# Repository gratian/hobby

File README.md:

# Hobby Projects

* kicad - electronics

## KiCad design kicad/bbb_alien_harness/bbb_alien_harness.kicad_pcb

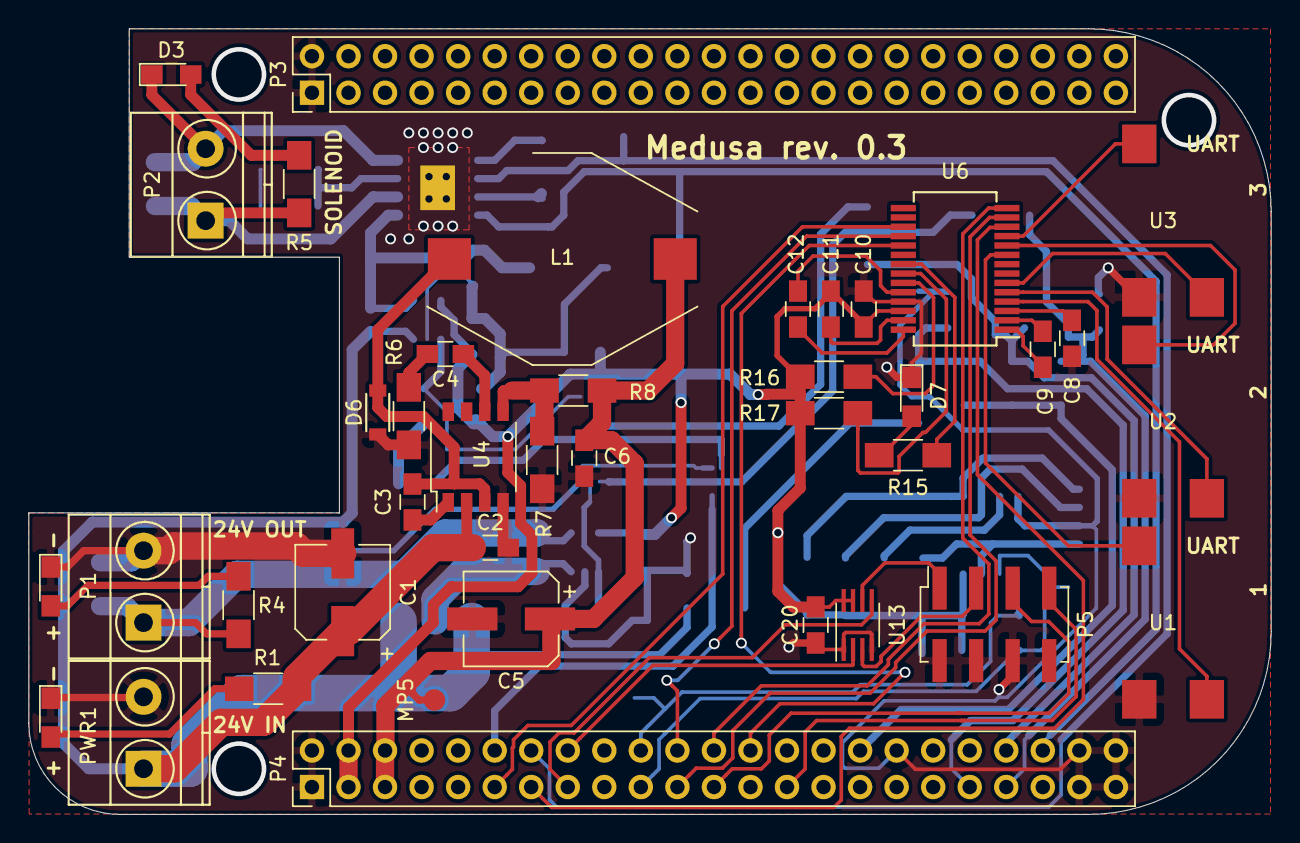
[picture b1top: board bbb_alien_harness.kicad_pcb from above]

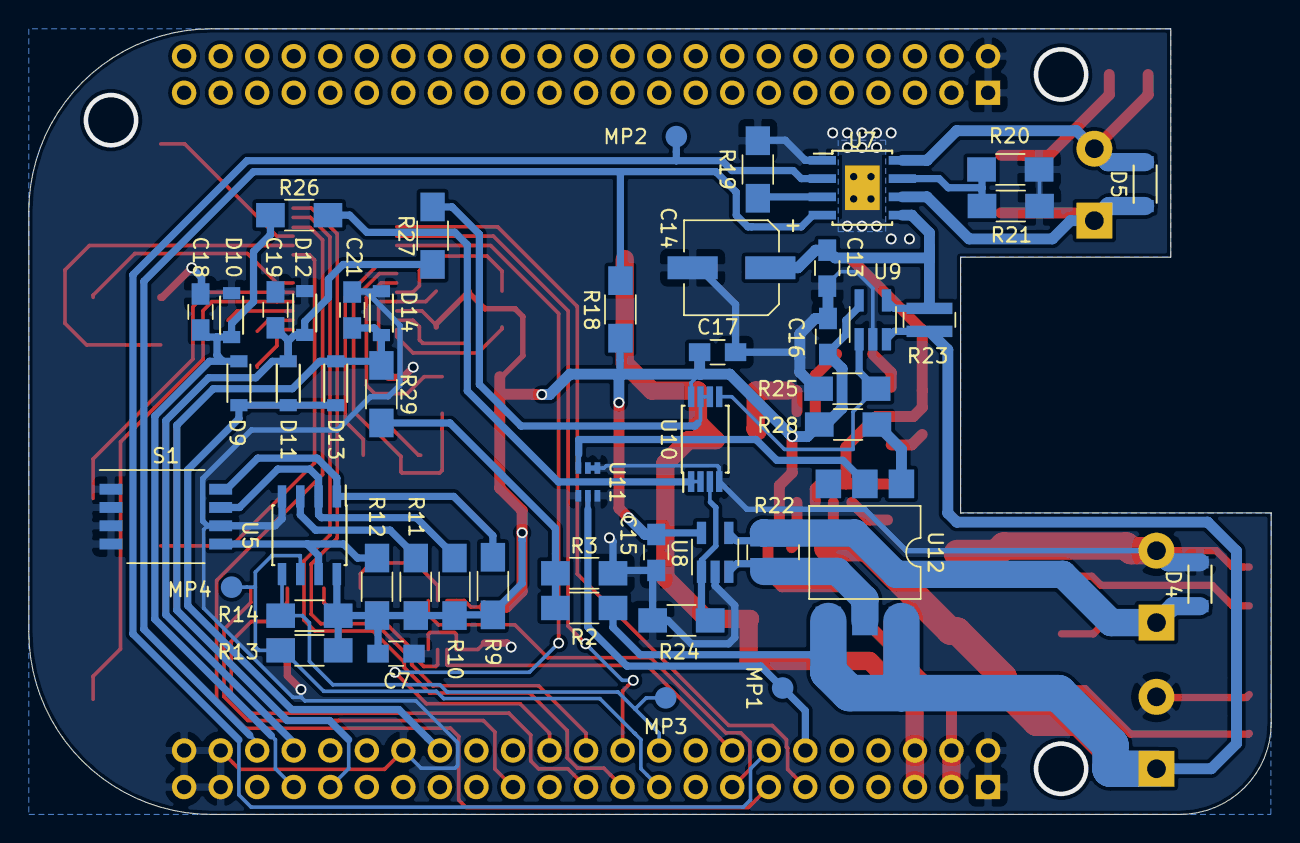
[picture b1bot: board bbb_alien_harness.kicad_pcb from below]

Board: 2 copper layers, 86.4 x 54.6 mm, 89 parts (49 on the bottom side), 67 nets.

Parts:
C1, C14: 47uF; CP_Elec_6.3x5.8
C2: 10uF; C_0805_HandSoldering
C3: 10nF; C_0805_HandSoldering
C4: 2.2nF; C_0805_HandSoldering
C5: 100uF; CP_Elec_6.3x5.8
C6: 1uF; C_0805_HandSoldering
C7, C8, C9, C10, C11, C12, C13, C15, C16, C17, C20: 0.1uF; C_0805_HandSoldering
C18, C19, C21: 1nF; C_0805_HandSoldering
D1: LXT0805YW; LED_0805_HandSoldering
D2, D7: LXT0805GW; LED_0805_HandSoldering
D3: D_1112H; LED_0805_HandSoldering
D4, D5, D6, D9, D10, D11, D12, D13, D14: DB2W40300L; SMD-Mini2-F3-B
L1: 33uH; L_Bourns-PM5022-330M-RC
MP1: SSR EN; Measurement_Point_Round-SMD-Pad_Small
MP2: PWM; Measurement_Point_Round-SMD-Pad_Small
MP3: I2C SDA; Measurement_Point_Round-SMD-Pad_Small
MP4: I2C SCL; Measurement_Point_Round-SMD-Pad_Small
MP5: +5V; Measurement_Point_Round-SMD-Pad_Small
P1: 24V OUT; TerminalBlock_Phoenix_MKDS1.5-2pol
P2: SOLENOID; TerminalBlock_Phoenix_MKDS1.5-2pol
P3: P8 on BBB; Pin_Header_Straight_2x23_Pitch2.54mm
P4: P9 on BBB; Pin_Header_Straight_2x23_Pitch2.54mm
P5: CONN_02X04; Socket_Strip_Straight_2x04_Pitch2.54mm_SMD
PWR1: 24V IN; TerminalBlock_Phoenix_MKDS1.5-2pol
R1, R4, R5: 2.4k; R_1206_HandSoldering
R2: 150k; R_1206_HandSoldering
R3, R7, R12, R16, R17, R18: 10k; R_1206_HandSoldering
R6: 8.2k; R_1206_HandSoldering
R8: 52k; R_1206_HandSoldering
R9, R10, R11: 4.7k; R_1206_HandSoldering
R13, R14: 5.6k; R_1206_HandSoldering
R15: 1k; R_1206_HandSoldering
R19: 100k; R_1206_HandSoldering
R20: 1; R_1206_HandSoldering
R21: 2; R_1206_HandSoldering
R22, R23: 0.020; R_0612
R24, R25: 75k; R_1206_HandSoldering
R26, R27, R29: 75; R_1206_HandSoldering
R28: 360; R_1206_HandSoldering
S1: SW_DIP_x4; SW_DIP_x4_W7.62mm_Slide_Copal_CHS-B
U1, U2, U3: SERIAL; SJ1-251X-SMT 2.5mm stereo jack
U4: ACT4065A; SOP-8_4.4x5mm_Pitch1.27mm
U5: 24C256; SOIC-8_3.9x4.9mm_Pitch1.27mm
U6: MAX3243; SSOP-28_5.3x10.2mm_Pitch0.65mm
U7: DRV8872; TI_SO-PowerPAD-8
U8, U9: INA138; SOT-23-5_HandSoldering
U10: AD8542; TSSOP-8_4.4x3mm_Pitch0.65mm
U11: DMC56404; SMini6-F3-B
U12: AQV251A; SMDIP-6_W9.53mm
U13: SN74LVC2G241; SSOP-8_2.95x2.8mm_Pitch0.65mm

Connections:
5V_REG: C5.1, C6.1, L1.2, MP5.1, P4.5, P4.6, R8.1
+3V3: C7.1, C10.2, C11.2, C15.1, C16.1, C17.1, C20.1, P4.3, P4.4, R9.1, R10.1, R11.1, R12.1, R13.1, R14.1, R16.1, R17.1, R18.1, R28.2, U5.8, U6.26, U8.5, U9.5, U10.8, U13.7, U13.8
+24V: C1.1, C2.1, PWR1.1, R1.1, R2.1, R23.1, U4.2, U9.3, U12.4, U12.6
/24V SSR/24V_OUT: R22.2, U8.3, U12.5
/POWER SENSE/OUT1: D4.1, P1.1, R4.1, R22.1, U8.4
/POWER SENSE/OUT2: C13.1, C14.1, R23.2, U7.5, U9.4
/POWER SENSE/sheet5AE7F055/IN: R26.2, U10.1, U10.2
/POWER SENSE/sheet5AE871AC/IN: R27.2, U10.6, U10.7
/SERIAL/RS232_RX1: U1.1, U6.4
/SERIAL/RS232_RX2: U2.1, U6.5
/SERIAL/RS232_RX3: U3.1, U6.6
/SERIAL/RS232_TX1: U1.2, U6.9
/SERIAL/RS232_TX2: U2.2, U6.10
/SERIAL/RS232_TX3: U3.2, U6.11
/SOLENOID DRIVER/S+: D5.1, P2.1, R5.1, U7.6
/SOLENOID DRIVER/S-: D3.1, D5.2, P2.2, U7.8
/sheet5B1360C9/IN: R2.2, R3.1, R29.2
AIN0: C18.1, D9.2, D10.1, P4.39, R26.1
AIN1: C19.1, D11.2, D12.1, P4.40, R27.1
AIN2: C21.1, D13.2, D14.1, P4.37, R29.1
EHRPWM1A: MP2.1, P4.14, U7.2
EHRPWM1B: P4.16, U13.2
GND: C1.2, C2.2, C5.2, C6.2, C7.2, C8.1, C10.1, C13.2, C14.2, C15.2, C16.2, C17.2, C18.2, C19.2, C20.2, C21.2, D1.1, D2.1, D4.2, D6.2, D7.1, D10.2, D12.2, D14.2, P1.2, P3.1, P3.2, P4.1, P4.2, P4.34, P4.43, P4.44, P4.45, P4.46, P5.2, P5.4, P5.6, P5.8, PWR1.2, R3.2, R6.2, R7.2, R19.2, R20.1, R21.1, R24.2, R25.2, S1.1, S1.2, S1.3, S1.4, S1.6, U1.3, U2.3, U3.3, U4.4, U5.4, U6.25, U7.1, U7.9, U8.2, U9.2, U10.4, U11.1, U11.3, U11.4, U11.5, U13.1, U13.4
GPIO0_7&GPIO3_18: P4.42, R18.2, U7.4
GPIO1_16: P4.15, U13.5
GPIO1_17: P4.23, P5.5
GPIO1_28: MP1.1, P4.12, U11.2
GPIO3_19: P4.27, P5.7
I2C2_SCL: MP4.1, P4.19, R13.2, U5.6
I2C2_SDA: MP3.1, P4.20, R14.2, U5.5
unnamed: C3.1, U4.1
unnamed: C3.2, D6.1, L1.1, U4.3
unnamed: C4.1, U4.6
unnamed: C4.2, R6.1
unnamed: C8.2, U6.3
unnamed: C9.1, U6.1
unnamed: C9.2, U6.2
unnamed: C11.1, U6.27
unnamed: C12.1, U6.28
unnamed: C12.2, U6.24
unnamed: D1.2, R1.2
unnamed: D2.2, R4.2
unnamed: D3.2, R5.2
unnamed: D7.2, R15.1
unnamed: P5.1, U13.6
unnamed: P5.3, U13.3
unnamed: R7.1, R8.2, U4.5
unnamed: R9.2, S1.8, U5.1
unnamed: R10.2, S1.7, U5.2
unnamed: R11.2, U5.3
unnamed: R12.2, S1.5, U5.7
unnamed: R15.2, U6.21
unnamed: R16.2, U6.23
unnamed: R17.2, U6.22
unnamed: R19.1, U7.3
unnamed: R20.2, R21.2, U7.7
unnamed: R24.1, U8.1, U10.3
unnamed: R25.1, U9.1, U10.5
unnamed: R28.1, U12.1
unnamed: U11.6, U12.2
UART1_RXD: P4.26, U6.19
UART1_TXD: P4.24, U6.14
UART2_RXD: P4.22, U6.18
UART2_TXD: P4.21, U6.13
UART4_RXD: P4.11, U6.17
UART4_TXD: P4.13, U6.12
VADC: D9.1, D11.1, D13.1, P4.32

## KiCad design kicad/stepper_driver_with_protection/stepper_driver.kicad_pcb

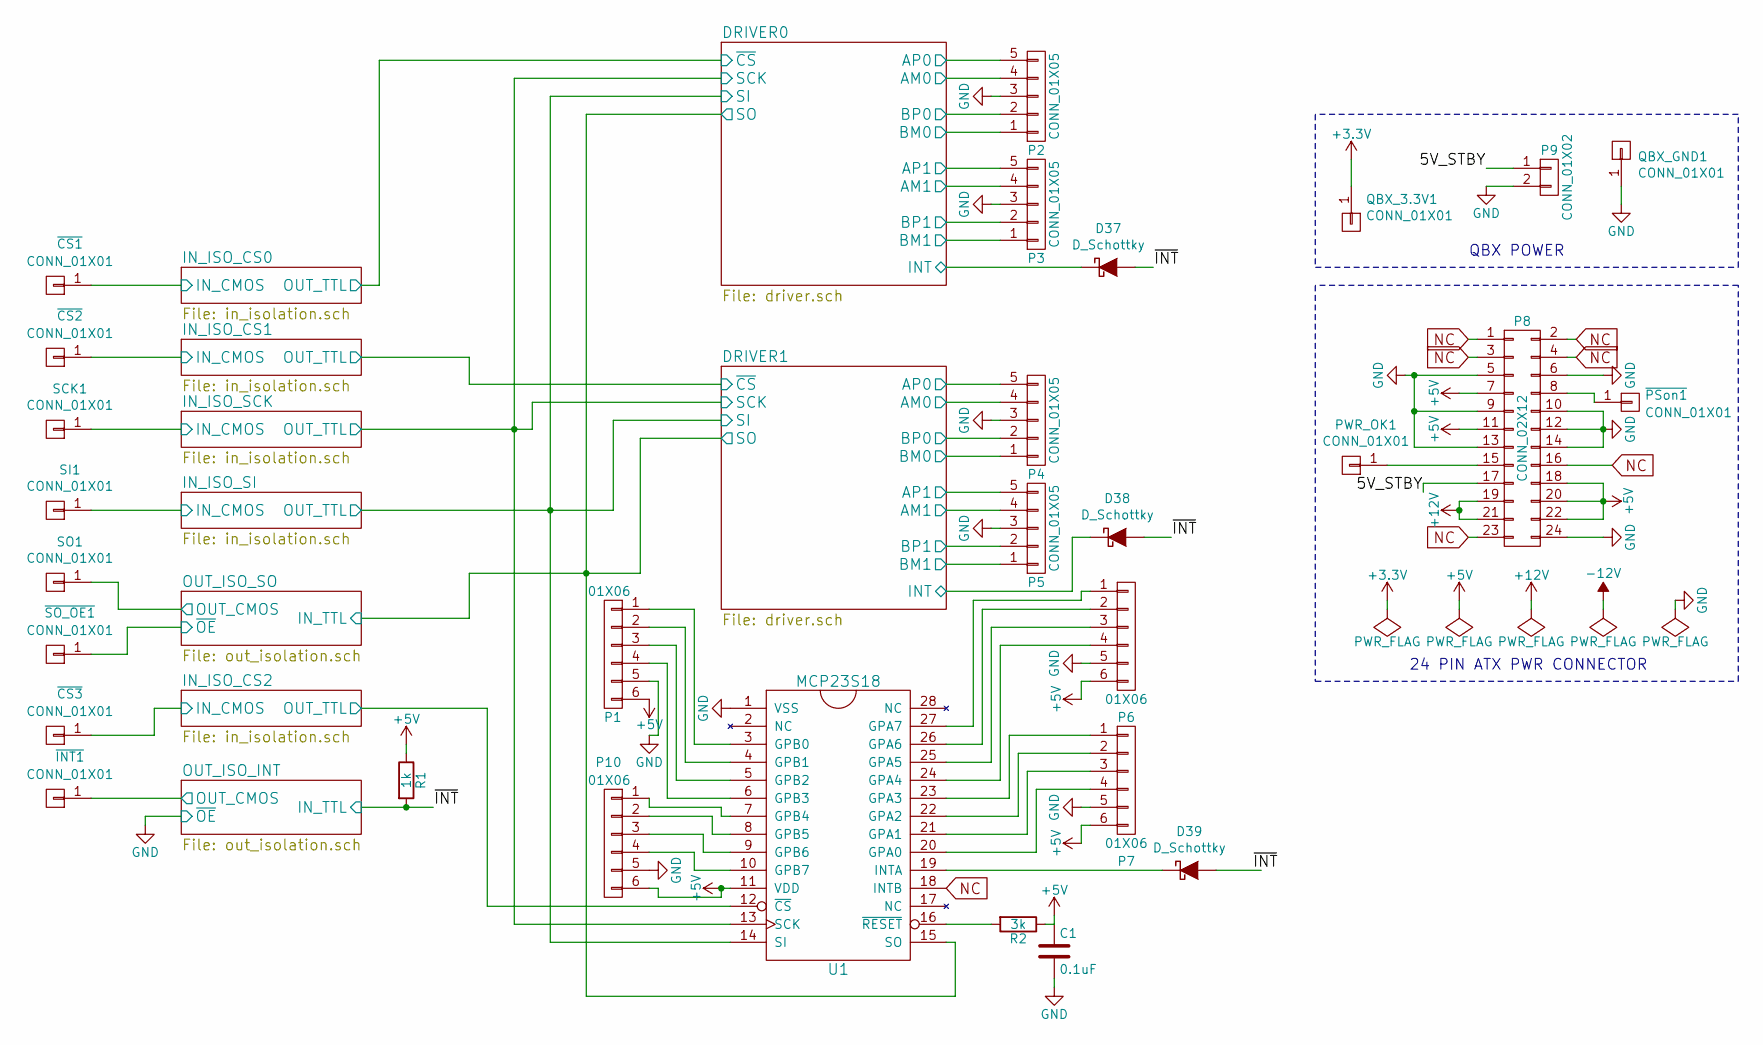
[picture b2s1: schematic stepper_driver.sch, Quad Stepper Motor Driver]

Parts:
C1: 0.1uF; C_1206_HandSoldering
D37, D38, D39: D_Schottky; Diode_DO-41_SOD81_Horizontal_RM10
P1, P6, P7, P10: 01X06; KF2EDGK-6_pin_Screw_Terminal_Block
P2, P3, P4, P5: CONN_01X05; TerminalBlock_Pheonix_PT-3.5mm_5pol
P8: CONN_02X12; Molex_MiniFit-JR-5556-24A_2x12x4.20mm_Straight
P9: CONN_01X02; PINHEAD1-2
PWR_OK1: CONN_01X01; SolderWirePad_single_0-8mmDrill
QBX_3.3V1: CONN_01X01; SolderWirePad_single_0-8mmDrill
QBX_GND1: CONN_01X01; SolderWirePad_single_0-8mmDrill
R1: 1k; R_1206_HandSoldering
R2: 3k; R_1206_HandSoldering
SCK1: CONN_01X01; SolderWirePad_single_0-8mmDrill
SI1: CONN_01X01; SolderWirePad_single_0-8mmDrill
SO1: CONN_01X01; SolderWirePad_single_0-8mmDrill
U1: MCP23S18; SOIC-28
~CS1, ~CS2, ~CS3: CONN_01X01; SolderWirePad_single_0-8mmDrill
~INT1: CONN_01X01; SolderWirePad_single_0-8mmDrill
~PSon1: CONN_01X01; SolderWirePad_single_0-8mmDrill
~SO_OE1: CONN_01X01; SolderWirePad_single_0-8mmDrill

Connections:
+3V3: QBX_3.3V1.1; also elsewhere on the board
+5V: C1.1, P1.6, P6.6, P7.6, P8.7, P8.11, P8.18, P8.20, P8.22, P10.6, R1.1, R2.1, U1.11 (VDD); also elsewhere on the board
+12V: P8.19, P8.21; also elsewhere on the board
/5V_STBY: P8.17, P9.1
/DRIVER0/AM0: P2.4; also elsewhere on the board
/DRIVER0/AM1: P3.4; also elsewhere on the board
/DRIVER0/AP0: P2.5; also elsewhere on the board
/DRIVER0/AP1: P3.5; also elsewhere on the board
/DRIVER0/BM0: P2.1; also elsewhere on the board
/DRIVER0/BM1: P3.1; also elsewhere on the board
/DRIVER0/BP0: P2.2; also elsewhere on the board
/DRIVER0/BP1: P3.2; also elsewhere on the board
/DRIVER0/INT: D37.1 (K); also elsewhere on the board
/DRIVER1/AM0: P4.4; also elsewhere on the board
/DRIVER1/AM1: P5.4; also elsewhere on the board
/DRIVER1/AP0: P4.5; also elsewhere on the board
/DRIVER1/AP1: P5.5; also elsewhere on the board
/DRIVER1/BM0: P4.1; also elsewhere on the board
/DRIVER1/BM1: P5.1; also elsewhere on the board
/DRIVER1/BP0: P4.2; also elsewhere on the board
/DRIVER1/BP1: P5.2; also elsewhere on the board
/DRIVER1/INT: D38.1 (K); also elsewhere on the board
/IN_ISO_CS2/OUT_TTL: U1.12 (~CS); also elsewhere on the board
/IN_ISO_SCK/IN_CMOS: SCK1.1; also elsewhere on the board
/IN_ISO_SCK/OUT_TTL: U1.13 (SCK); also elsewhere on the board
/IN_ISO_SI/IN_CMOS: SI1.1; also elsewhere on the board
/IN_ISO_SI/OUT_TTL: U1.14 (SI); also elsewhere on the board
/OUT_ISO_SO/IN_TTL: U1.15 (SO); also elsewhere on the board
/OUT_ISO_SO/OUT_CMOS: SO1.1; also elsewhere on the board
/~INT: D37.2 (A), D38.2 (A), D39.2 (A), R1.2; also elsewhere on the board
GND: C1.2, P1.5, P2.3, P3.3, P4.3, P5.3, P6.5, P7.5, P8.5, P8.6, P8.9, P8.10, P8.12, P8.13, P8.14, P8.24, P9.2, P10.5, QBX_GND1.1, U1.1 (VSS); also elsewhere on the board
NC: P8.1, P8.2, P8.3, P8.4, P8.16, P8.23, U1.18 (INTB); also elsewhere on the board
unnamed: D39.1 (K), U1.19 (INTA)
unnamed: P1.1, U1.3 (GPB0)
unnamed: P1.2, U1.4 (GPB1)
unnamed: P1.3, U1.5 (GPB2)
unnamed: P1.4, U1.6 (GPB3)
unnamed: P6.1, U1.27 (GPA7)
unnamed: P6.2, U1.26 (GPA6)
unnamed: P6.3, U1.25 (GPA5)
unnamed: P6.4, U1.24 (GPA4)
unnamed: P7.1, U1.23 (GPA3)
unnamed: P7.2, U1.22 (GPA2)
unnamed: P7.3, U1.21 (GPA1)
unnamed: P7.4, U1.20 (GPA0)
unnamed: P8.8, ~PSon1.1
unnamed: P8.15, PWR_OK1.1
unnamed: P10.1, U1.7 (GPB4)
unnamed: P10.2, U1.8 (GPB5)
unnamed: P10.3, U1.9 (GPB6)
unnamed: P10.4, U1.10 (GPB7)
unnamed: R2.2, U1.16 (~RESET)

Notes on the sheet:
24 PIN ATX PWR CONNECTOR
QBX POWER

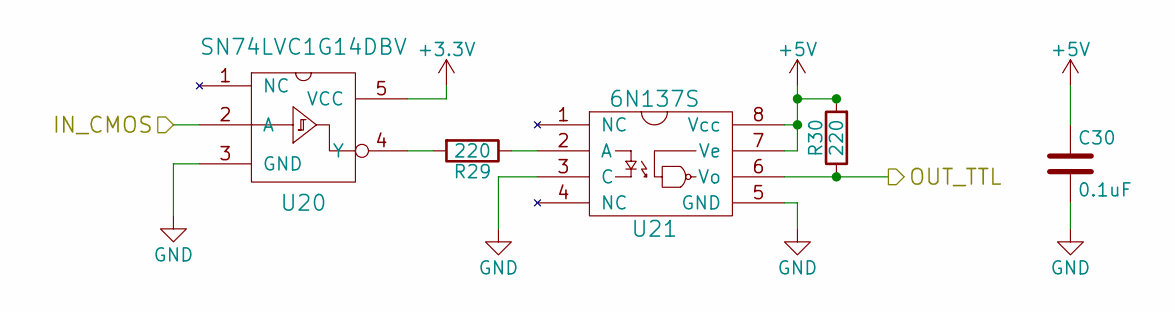
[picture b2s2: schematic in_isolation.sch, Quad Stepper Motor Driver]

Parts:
C2: 0.1uF; C_1206_HandSoldering
R3, R4: 220; R_1206_HandSoldering
U2: SN74LVC1G14DBV; SOT-23-5
U3: 6N137S; SMD-8

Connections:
+3V3: U2.5 (VCC); also elsewhere on the board
+5V: C2.1, R4.2, U3.7 (Ve), U3.8 (Vcc); also elsewhere on the board
/IN_ISO_CS0/IN_CMOS: U2.2 (A)
/IN_ISO_CS0/OUT_TTL: R4.1, U3.6 (Vo); also elsewhere on the board
GND: C2.2, U2.3 (GND), U3.3 (C), U3.5 (GND); also elsewhere on the board
unnamed: R3.1, U3.2 (A)
unnamed: R3.2, U2.4 (Y)

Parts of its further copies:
C3, C5, C6, C30: 0.1uF; C_1206_HandSoldering
R5, R6, R9, R10, R11, R12, R29, R30: 220; R_1206_HandSoldering
U4, U8, U10, U20: SN74LVC1G14DBV; SOT-23-5
U5, U9, U11, U21: 6N137S; SMD-8

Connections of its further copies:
+3V3: U4.5 (VCC), U8.5 (VCC), U10.5 (VCC), U20.5 (VCC); also elsewhere on the board
+5V: C3.1, C5.1, C6.1, C30.1, R6.2, R10.2, R12.2, R30.2, U5.7 (Ve), U5.8 (Vcc), U9.7 (Ve), U9.8 (Vcc), U11.7 (Ve), U11.8 (Vcc), U21.7 (Ve), U21.8 (Vcc); also elsewhere on the board
/IN_ISO_CS1/IN_CMOS: U10.2 (A)
/IN_ISO_CS1/OUT_TTL: R12.1, U11.6 (Vo); also elsewhere on the board
/IN_ISO_CS2/IN_CMOS: U20.2 (A)
/IN_ISO_CS2/OUT_TTL: R30.1, U21.6 (Vo); also elsewhere on the board
/IN_ISO_SCK/IN_CMOS: U4.2 (A); also elsewhere on the board
/IN_ISO_SCK/OUT_TTL: R6.1, U5.6 (Vo); also elsewhere on the board
/IN_ISO_SI/IN_CMOS: U8.2 (A); also elsewhere on the board
/IN_ISO_SI/OUT_TTL: R10.1, U9.6 (Vo); also elsewhere on the board
GND: C3.2, C5.2, C6.2, C30.2, U4.3 (GND), U5.3 (C), U5.5 (GND), U8.3 (GND), U9.3 (C), U9.5 (GND), U10.3 (GND), U11.3 (C), U11.5 (GND), U20.3 (GND), U21.3 (C), U21.5 (GND); also elsewhere on the board
unnamed: R5.1, U5.2 (A)
unnamed: R5.2, U4.4 (Y)
unnamed: R9.1, U9.2 (A)
unnamed: R9.2, U8.4 (Y)
unnamed: R11.1, U11.2 (A)
unnamed: R11.2, U10.4 (Y)
unnamed: R29.1, U21.2 (A)
unnamed: R29.2, U20.4 (Y)

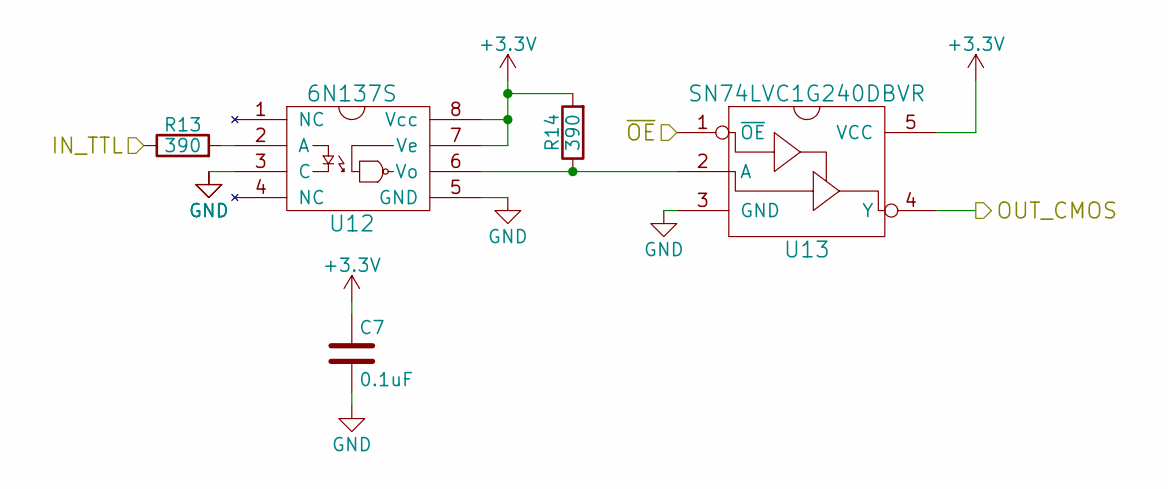
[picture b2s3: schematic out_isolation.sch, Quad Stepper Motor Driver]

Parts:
C4: 0.1uF; C_1206_HandSoldering
R7, R8: 390; R_1206_HandSoldering
U6: 6N137S; SMD-8
U7: SN74LVC1G240DBVR; SOT-23-5

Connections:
+3V3: C4.1, R8.2, U6.7 (Ve), U6.8 (Vcc), U7.5 (VCC); also elsewhere on the board
/OUT_ISO_SO/IN_TTL: R7.1; also elsewhere on the board
/OUT_ISO_SO/OUT_CMOS: U7.4 (Y); also elsewhere on the board
/OUT_ISO_SO/~OE: U7.1 (~OE)
GND: C4.2, U6.3 (C), U6.5 (GND), U7.3 (GND); also elsewhere on the board
unnamed: R7.2, U6.2 (A)
unnamed: R8.1, U6.6 (Vo), U7.2 (A)

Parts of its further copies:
C7: 0.1uF; C_1206_HandSoldering
R13, R14: 390; R_1206_HandSoldering
U12: 6N137S; SMD-8
U13: SN74LVC1G240DBVR; SOT-23-5

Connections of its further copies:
+3V3: C7.1, R14.2, U12.7 (Ve), U12.8 (Vcc), U13.5 (VCC); also elsewhere on the board
/OUT_ISO_INT/OUT_CMOS: U13.4 (Y)
/~INT: R13.1; also elsewhere on the board
GND: C7.2, U12.3 (C), U12.5 (GND), U13.1 (~OE), U13.3 (GND); also elsewhere on the board
unnamed: R13.2, U12.2 (A)
unnamed: R14.1, U12.6 (Vo), U13.2 (A)

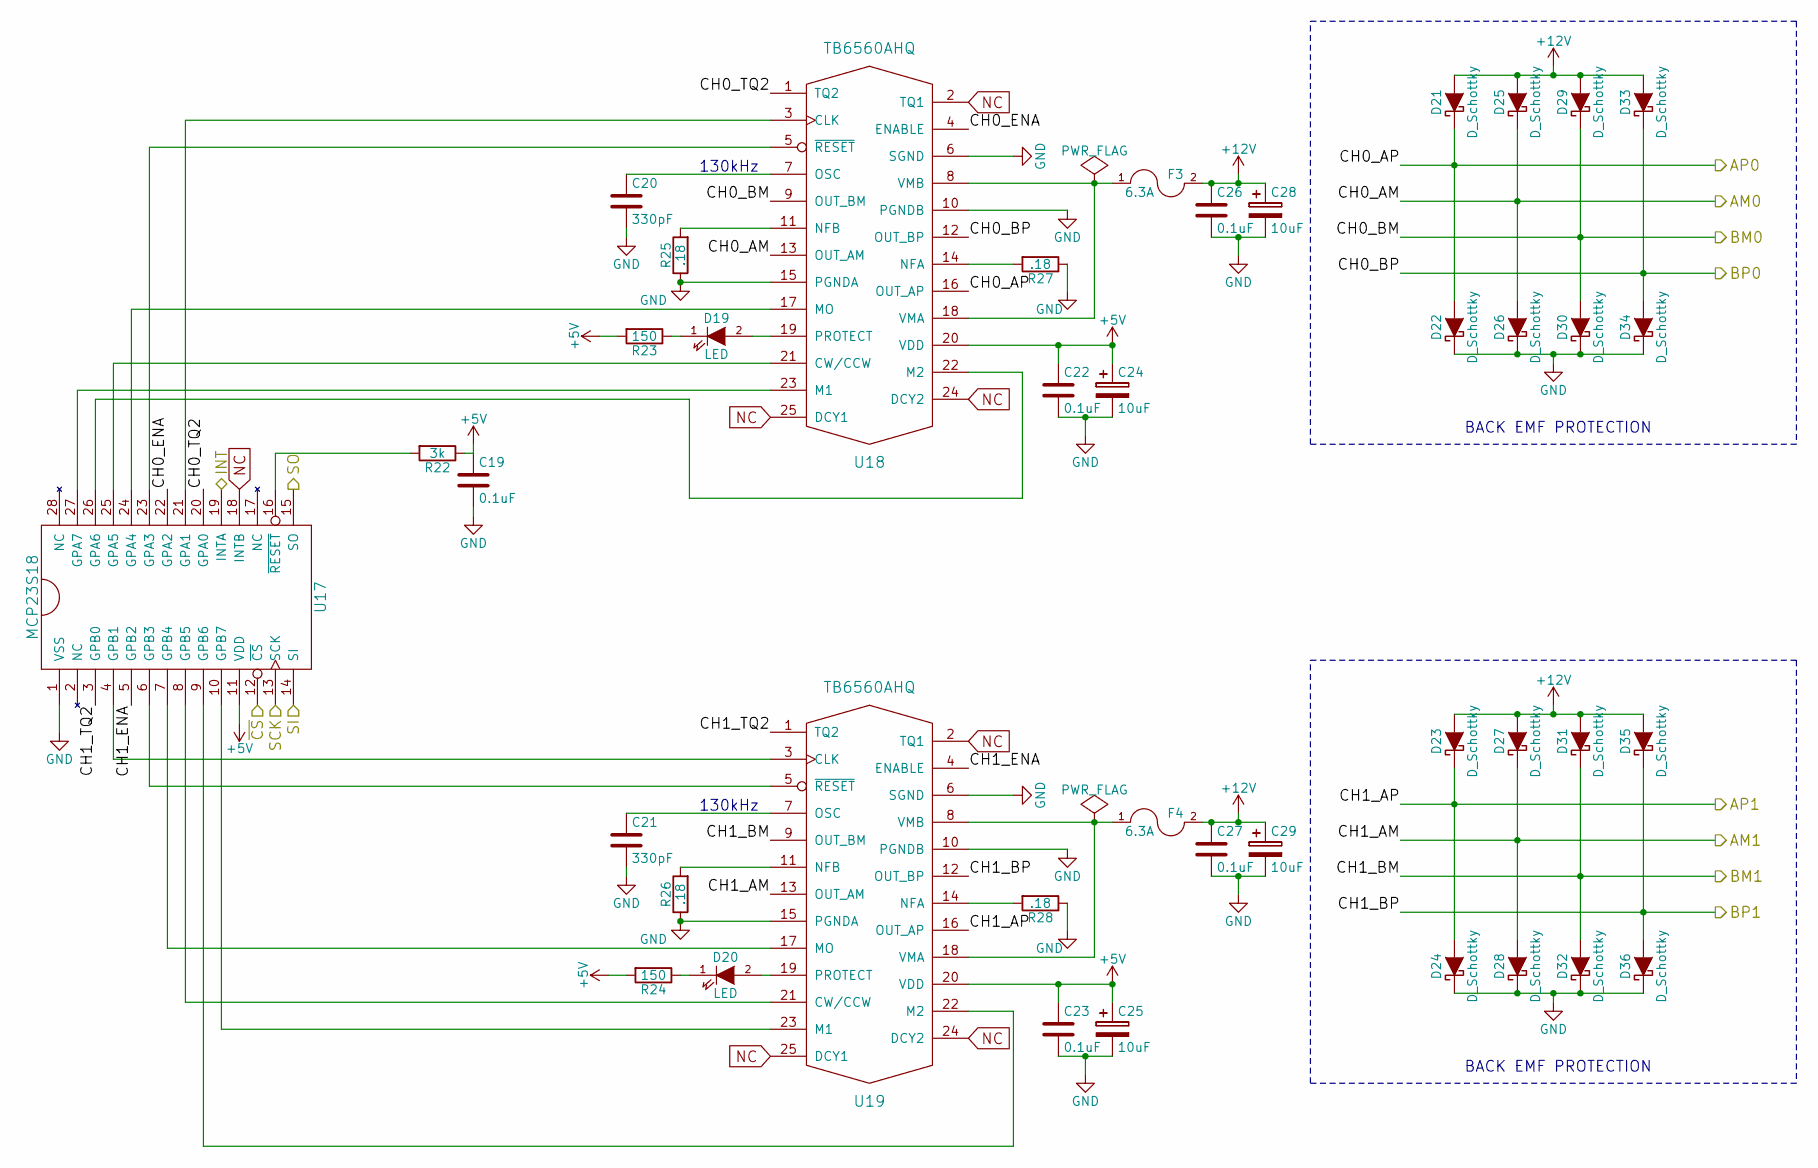
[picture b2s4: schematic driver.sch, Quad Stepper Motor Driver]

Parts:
C8, C11, C12, C15, C16: 0.1uF; C_1206_HandSoldering
C9, C10: 330pF; C_0805_HandSoldering
C13, C14, C17, C18: 10uF; c_elec_4x5.3
D1, D2: LED; LED-3MM
D3, D4, D5, D6, D7, D8, D9, D10, D11, D12, D13, D14, D15, D16, D17, D18: D_Schottky; SMD-Mini2-F3-B
F1, F2: 6.3A; Fuse_SMD2410
R15: 3k; R_1206_HandSoldering
R16, R17: 150; R_1206_HandSoldering
R18, R19, R20, R21: .18; R_1206_HandSoldering
U14: MCP23S18; SOIC-28
U15, U16: TB6560AHQ; HZIP25-P-1.27

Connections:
+5V: C8.1, C11.1, C12.1, C13.1, C14.1, R15.1, R16.2, R17.2, U14.11 (VDD), U15.20 (VDD), U16.20 (VDD); also elsewhere on the board
+12V: C15.1, C16.1, C17.1, C18.1, D3.2 (A), D5.2 (A), D7.2 (A), D9.2 (A), D11.2 (A), D13.2 (A), D15.2 (A), D17.2 (A), F1.2, F2.2; also elsewhere on the board
/DRIVER0/AM0: D7.1 (K), D8.2 (A), U15.13 (OUT_AM); also elsewhere on the board
/DRIVER0/AM1: D9.1 (K), D10.2 (A), U16.13 (OUT_AM); also elsewhere on the board
/DRIVER0/AP0: D3.1 (K), D4.2 (A), U15.16 (OUT_AP); also elsewhere on the board
/DRIVER0/AP1: D5.1 (K), D6.2 (A), U16.16 (OUT_AP); also elsewhere on the board
/DRIVER0/BM0: D11.1 (K), D12.2 (A), U15.9 (OUT_BM); also elsewhere on the board
/DRIVER0/BM1: D13.1 (K), D14.2 (A), U16.9 (OUT_BM); also elsewhere on the board
/DRIVER0/BP0: D15.1 (K), D16.2 (A), U15.12 (OUT_BP); also elsewhere on the board
/DRIVER0/BP1: D17.1 (K), D18.2 (A), U16.12 (OUT_BP); also elsewhere on the board
/DRIVER0/CH0_ENA: U14.22 (GPA2), U15.4 (ENABLE)
/DRIVER0/CH0_TQ2: U14.20 (GPA0), U15.1 (TQ2)
/DRIVER0/CH1_ENA: U14.5 (GPB2), U16.4 (ENABLE)
/DRIVER0/CH1_TQ2: U14.3 (GPB0), U16.1 (TQ2)
/DRIVER0/INT: U14.19 (INTA); also elsewhere on the board
/IN_ISO_CS0/OUT_TTL: U14.12 (~CS); also elsewhere on the board
/IN_ISO_SCK/OUT_TTL: U14.13 (SCK); also elsewhere on the board
/IN_ISO_SI/OUT_TTL: U14.14 (SI); also elsewhere on the board
/OUT_ISO_SO/IN_TTL: U14.15 (SO); also elsewhere on the board
GND: C8.2, C9.2, C10.2, C11.2, C12.2, C13.2, C14.2, C15.2, C16.2, C17.2, C18.2, D4.1 (K), D6.1 (K), D8.1 (K), D10.1 (K), D12.1 (K), D14.1 (K), D16.1 (K), D18.1 (K), R18.1, R19.1, R20.1, R21.1, U14.1 (VSS), U15.6 (SGND), U15.10 (PGNDB), U15.15 (PGNDA), U16.6 (SGND), U16.10 (PGNDB), U16.15 (PGNDA); also elsewhere on the board
NC: U14.18 (INTB), U15.2 (TQ1), U15.24 (DCY2), U15.25 (DCY1), U16.2 (TQ1), U16.24 (DCY2), U16.25 (DCY1); also elsewhere on the board
unnamed: C9.1, U15.7 (OSC)
unnamed: C10.1, U16.7 (OSC)
unnamed: D1.1 (K), R16.1
unnamed: D1.2 (A), U15.19 (PROTECT)
unnamed: D2.1 (K), R17.1
unnamed: D2.2 (A), U16.19 (PROTECT)
unnamed: F1.1, U15.8 (VMB), U15.18 (VMA)
unnamed: F2.1, U16.8 (VMB), U16.18 (VMA)
unnamed: R15.2, U14.16 (~RESET)
unnamed: R18.2, U15.11 (NFB)
unnamed: R19.2, U16.11 (NFB)
unnamed: R20.2, U15.14 (NFA)
unnamed: R21.2, U16.14 (NFA)
unnamed: U14.4 (GPB1), U16.3 (CLK)
unnamed: U14.6 (GPB3), U16.5 (~RESET)
unnamed: U14.7 (GPB4), U16.17 (MO)
unnamed: U14.8 (GPB5), U16.21 (CW/CCW)
unnamed: U14.9 (GPB6), U16.22 (M2)
unnamed: U14.10 (GPB7), U16.23 (M1)
unnamed: U14.21 (GPA1), U15.3 (CLK)
unnamed: U14.23 (GPA3), U15.5 (~RESET)
unnamed: U14.24 (GPA4), U15.17 (MO)
unnamed: U14.25 (GPA5), U15.21 (CW/CCW)
unnamed: U14.26 (GPA6), U15.22 (M2)
unnamed: U14.27 (GPA7), U15.23 (M1)

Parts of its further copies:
C19, C22, C23, C26, C27: 0.1uF; C_1206_HandSoldering
C20, C21: 330pF; C_0805_HandSoldering
C24, C25, C28, C29: 10uF; c_elec_4x5.3
D19, D20: LED; LED-3MM
D21, D22, D23, D24, D25, D26, D27, D28, D29, D30, D31, D32, D33, D34, D35, D36: D_Schottky; SMD-Mini2-F3-B
F3, F4: 6.3A; Fuse_SMD2410
R22: 3k; R_1206_HandSoldering
R23, R24: 150; R_1206_HandSoldering
R25, R26, R27, R28: .18; R_1206_HandSoldering
U17: MCP23S18; SOIC-28
U18, U19: TB6560AHQ; HZIP25-P-1.27

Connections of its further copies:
+5V: C19.1, C22.1, C23.1, C24.1, C25.1, R22.1, R23.2, R24.2, U17.11 (VDD), U18.20 (VDD), U19.20 (VDD); also elsewhere on the board
+12V: C26.1, C27.1, C28.1, C29.1, D21.2 (A), D23.2 (A), D25.2 (A), D27.2 (A), D29.2 (A), D31.2 (A), D33.2 (A), D35.2 (A), F3.2, F4.2; also elsewhere on the board
/DRIVER1/AM0: D25.1 (K), D26.2 (A), U18.13 (OUT_AM); also elsewhere on the board
/DRIVER1/AM1: D27.1 (K), D28.2 (A), U19.13 (OUT_AM); also elsewhere on the board
/DRIVER1/AP0: D21.1 (K), D22.2 (A), U18.16 (OUT_AP); also elsewhere on the board
/DRIVER1/AP1: D23.1 (K), D24.2 (A), U19.16 (OUT_AP); also elsewhere on the board
/DRIVER1/BM0: D29.1 (K), D30.2 (A), U18.9 (OUT_BM); also elsewhere on the board
/DRIVER1/BM1: D31.1 (K), D32.2 (A), U19.9 (OUT_BM); also elsewhere on the board
/DRIVER1/BP0: D33.1 (K), D34.2 (A), U18.12 (OUT_BP); also elsewhere on the board
/DRIVER1/BP1: D35.1 (K), D36.2 (A), U19.12 (OUT_BP); also elsewhere on the board
/DRIVER1/CH0_ENA: U17.22 (GPA2), U18.4 (ENABLE)
/DRIVER1/CH0_TQ2: U17.20 (GPA0), U18.1 (TQ2)
/DRIVER1/CH1_ENA: U17.5 (GPB2), U19.4 (ENABLE)
/DRIVER1/CH1_TQ2: U17.3 (GPB0), U19.1 (TQ2)
/DRIVER1/INT: U17.19 (INTA); also elsewhere on the board
/IN_ISO_CS1/OUT_TTL: U17.12 (~CS); also elsewhere on the board
/IN_ISO_SCK/OUT_TTL: U17.13 (SCK); also elsewhere on the board
/IN_ISO_SI/OUT_TTL: U17.14 (SI); also elsewhere on the board
/OUT_ISO_SO/IN_TTL: U17.15 (SO); also elsewhere on the board
GND: C19.2, C20.2, C21.2, C22.2, C23.2, C24.2, C25.2, C26.2, C27.2, C28.2, C29.2, D22.1 (K), D24.1 (K), D26.1 (K), D28.1 (K), D30.1 (K), D32.1 (K), D34.1 (K), D36.1 (K), R25.1, R26.1, R27.1, R28.1, U17.1 (VSS), U18.6 (SGND), U18.10 (PGNDB), U18.15 (PGNDA), U19.6 (SGND), U19.10 (PGNDB), U19.15 (PGNDA); also elsewhere on the board
NC: U17.18 (INTB), U18.2 (TQ1), U18.24 (DCY2), U18.25 (DCY1), U19.2 (TQ1), U19.24 (DCY2), U19.25 (DCY1); also elsewhere on the board
unnamed: C20.1, U18.7 (OSC)
unnamed: C21.1, U19.7 (OSC)
unnamed: D19.1 (K), R23.1
unnamed: D19.2 (A), U18.19 (PROTECT)
unnamed: D20.1 (K), R24.1
unnamed: D20.2 (A), U19.19 (PROTECT)
unnamed: F3.1, U18.8 (VMB), U18.18 (VMA)
unnamed: F4.1, U19.8 (VMB), U19.18 (VMA)
unnamed: R22.2, U17.16 (~RESET)
unnamed: R25.2, U18.11 (NFB)
unnamed: R26.2, U19.11 (NFB)
unnamed: R27.2, U18.14 (NFA)
unnamed: R28.2, U19.14 (NFA)
unnamed: U17.4 (GPB1), U19.3 (CLK)
unnamed: U17.6 (GPB3), U19.5 (~RESET)
unnamed: U17.7 (GPB4), U19.17 (MO)
unnamed: U17.8 (GPB5), U19.21 (CW/CCW)
unnamed: U17.9 (GPB6), U19.22 (M2)
unnamed: U17.10 (GPB7), U19.23 (M1)
unnamed: U17.21 (GPA1), U18.3 (CLK)
unnamed: U17.23 (GPA3), U18.5 (~RESET)
unnamed: U17.24 (GPA4), U18.17 (MO)
unnamed: U17.25 (GPA5), U18.21 (CW/CCW)
unnamed: U17.26 (GPA6), U18.22 (M2)
unnamed: U17.27 (GPA7), U18.23 (M1)

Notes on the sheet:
BACK EMF PROTECTION
130kHz

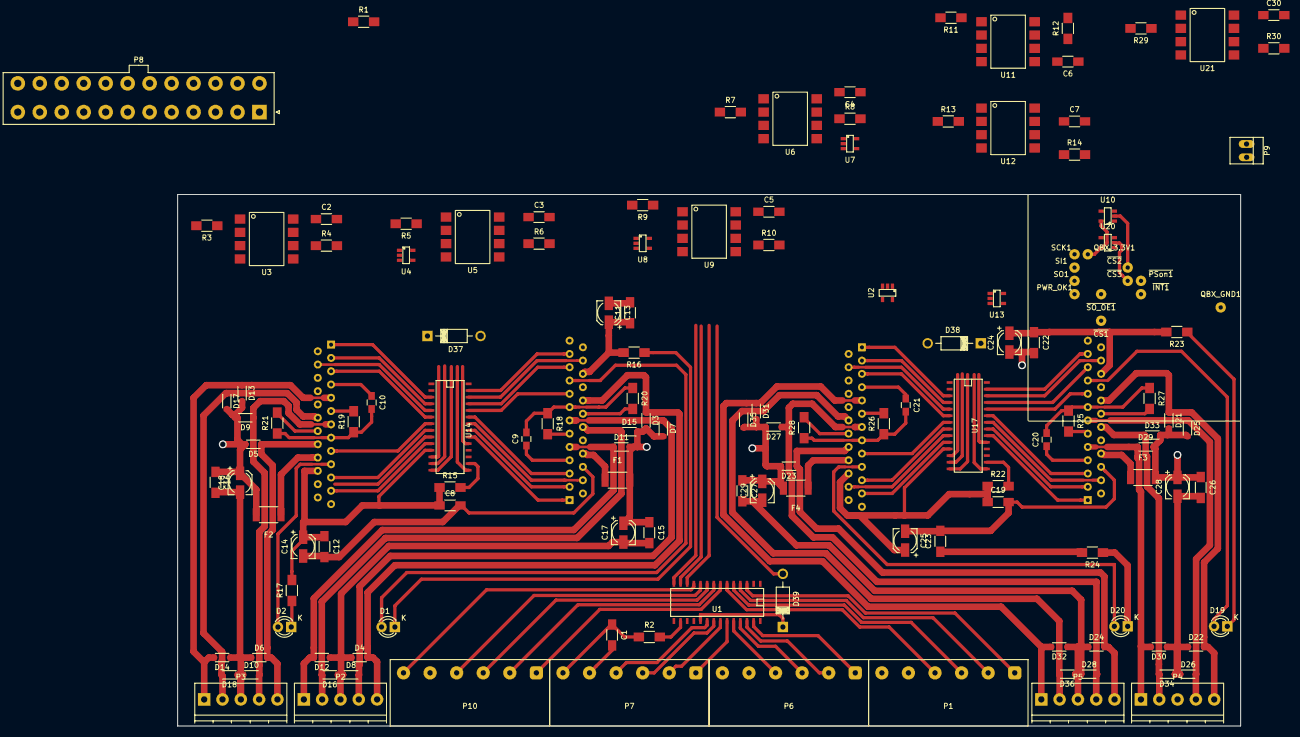
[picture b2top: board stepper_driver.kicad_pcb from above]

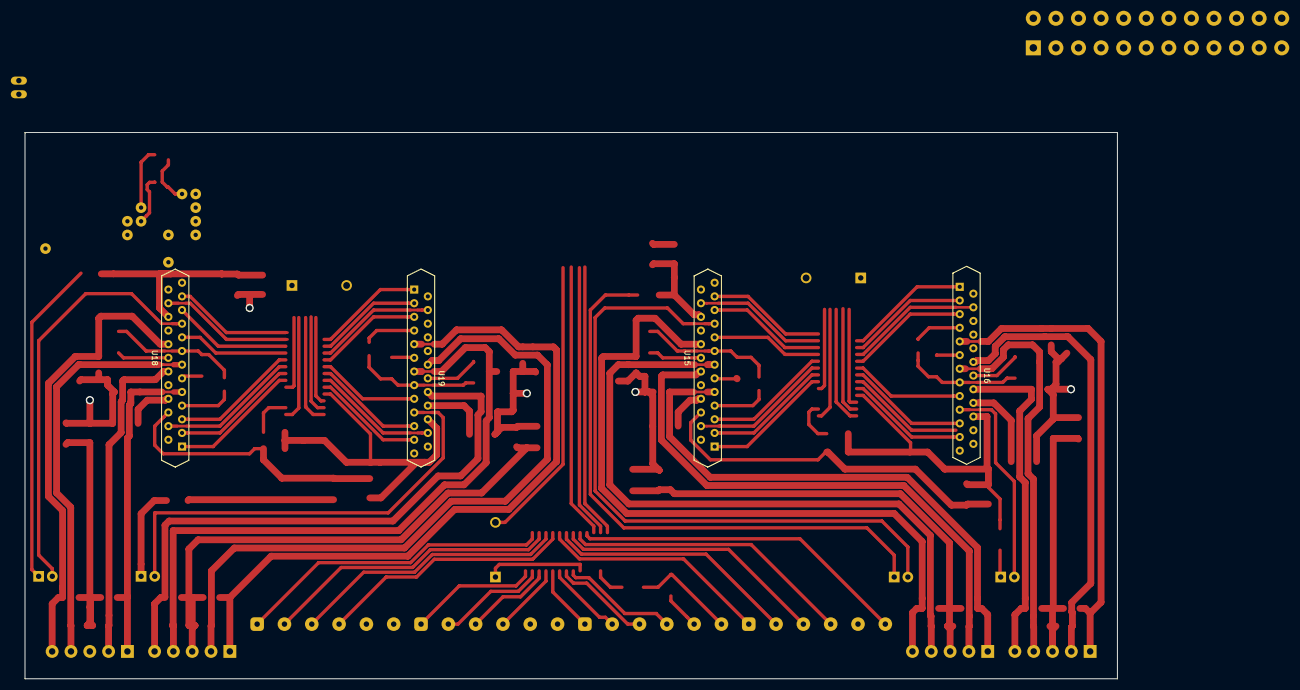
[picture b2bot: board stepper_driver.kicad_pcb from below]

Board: 2 copper layers, 203.2 x 101.6 mm, 140 parts (4 on the bottom side), 125 nets.

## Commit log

2015-03-25 kicad: Add inital project for bipolar stepper driver
2015-03-25 kicad,library: Fix documentation paths
2018-04-12 stepper_driver: new revision
    Forgot the history on this one. If anybody is watching. Sorry :(
    Moved datahseets into project folder.
    I guess I've added some footprints too.
2018-04-12 stepper_driver_with_protection: New design.
2019-04-03 library: new updates from upstream kicad
2019-04-03 bbb_alien_harness: medusa prototype (ver. 0.3)
    This is the first manufactured prototype of the Medusa Beagle Bone
    Black cape ver 0.3.
